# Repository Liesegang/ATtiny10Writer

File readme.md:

## Documents
+ http://akizukidenshi.com/download/ds/useconn/BH-XXSG.pdf
+ http://www.aitendo.com/product/7348
+ http://akizukidenshi.com/catalog/g/gI-04575/
+ https://make.kosakalab.com/make/electronic-work/arduino-ide/test_gen_avrisp-mk2/

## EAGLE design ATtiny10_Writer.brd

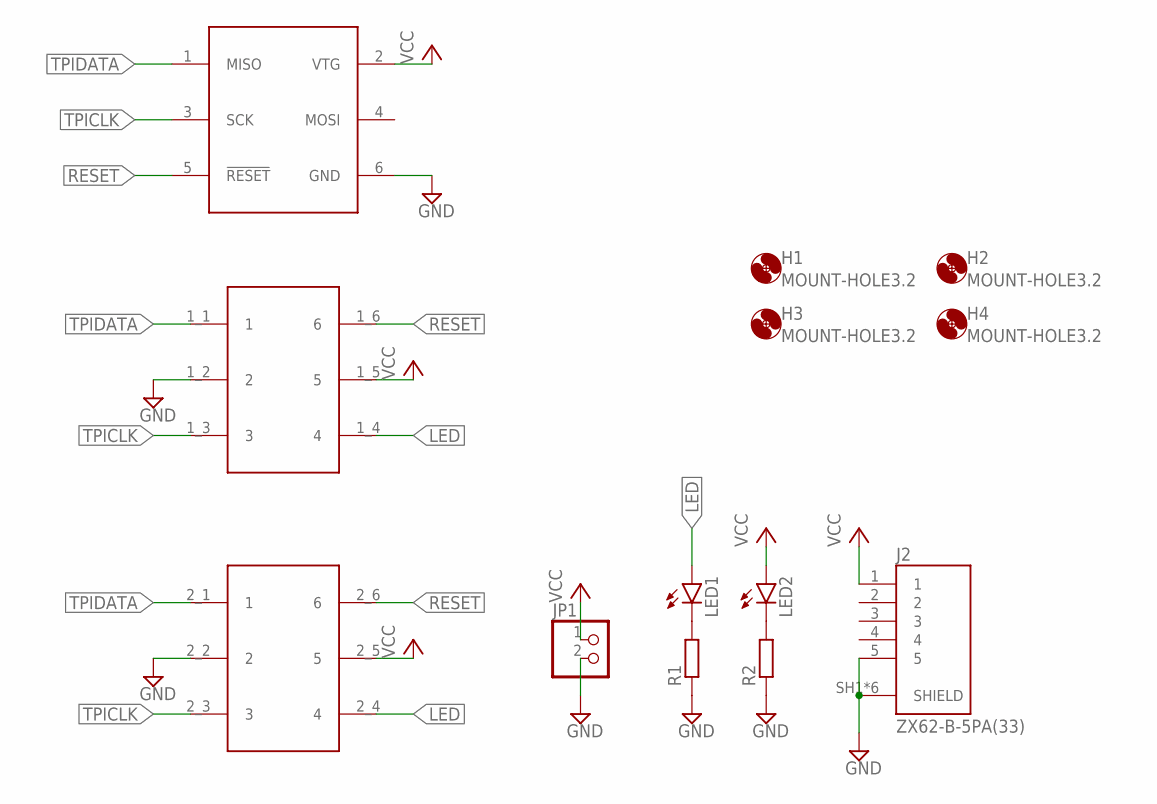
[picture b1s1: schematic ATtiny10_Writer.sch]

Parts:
CON1: AVR_ISP
H1, H2, H3, H4: MOUNT-HOLE3.2; 3,2
J1: SOT23-6_2_SOCKET; IC_SOCKET_051-2317-060
J2: ZX62-B-5PA(33); HRS_ZX62-B-5PA(33)
JP1: PINHD-1X2; 1X02
LED1, LED2: LEDCHIP-LED0603; CHIP-LED0603
R1, R2: R-EU_R0603; R0603

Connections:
GND: CON1.6 (GND), J1.1_2 (2), J1.2_2 (2), J2.5, J2.SH1 (SHIELD), J2.SH2 (SHIELD), J2.SH3 (SHIELD), J2.SH4 (SHIELD), J2.SH5 (SHIELD), J2.SH6 (SHIELD), JP1.2, R1.1, R2.1
LED: J1.1_4 (4), J1.2_4 (4), LED1.A
unnamed: LED1.C, R1.2
unnamed: LED2.C, R2.2
RESET: CON1.5 (!RESET), J1.1_6 (6), J1.2_6 (6)
TPICLK: CON1.3 (SCK), J1.1_3 (3), J1.2_3 (3)
TPIDATA: CON1.1 (MISO), J1.1_1 (1), J1.2_1 (1)
VCC: CON1.2 (VTG), J1.1_5 (5), J1.2_5 (5), J2.1, JP1.1, LED2.A

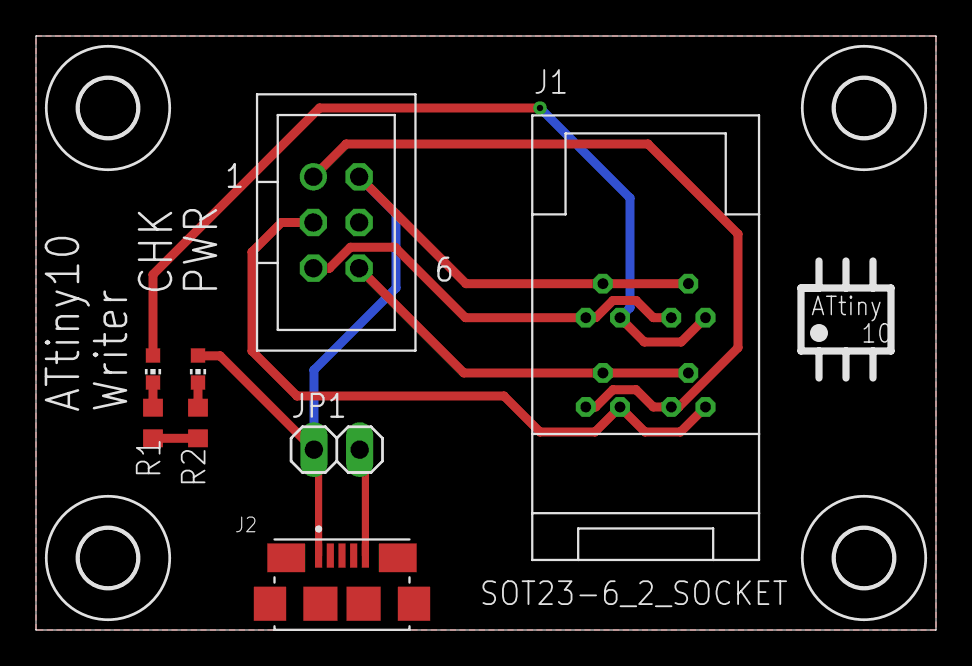
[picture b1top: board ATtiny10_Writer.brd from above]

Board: 2 copper layers, 50.0 x 33.0 mm, 12 parts (0 on the bottom side), 8 nets.

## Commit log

2019-08-27 add *.zip and gerber/ to .gitignore
2019-08-27 add readme
2019-08-27 complete all
